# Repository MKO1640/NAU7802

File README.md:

# NAU7802

first try to make a PCB Breakout for NAU7802 

BOM:
1 x NAU7802SGI SOIC-16_3.9x9.9mm_P1.27mm
1 x PinHeader_1x06_P2.54mm_Vertical
1 x PinHeader_1x04_P2.54mm_Vertical
2 x PinHeader_1x01_P2.54mm_Vertical
4 x R_0805_2012Metric 47 Ohm 
4 x C_0805_2012Metric 0,1uF
2 x C_0805_2012Metric   1uF
1 x Wago_734-135_1x05_P3.50mm_Vertical
1 x C_0805_2012Metric 330pF

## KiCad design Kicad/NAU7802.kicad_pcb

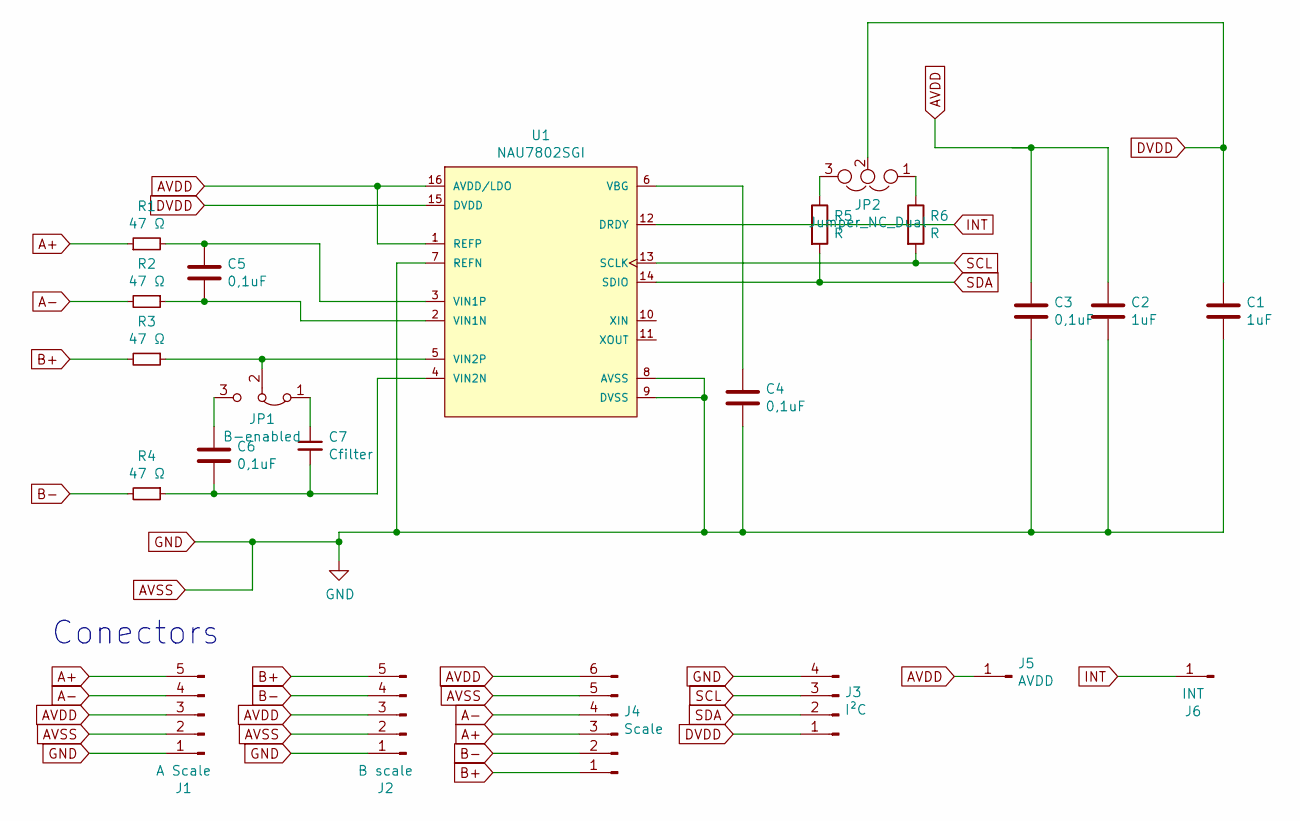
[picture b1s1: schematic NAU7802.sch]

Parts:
C1, C2: 1uF; C_0805_2012Metric
C3, C4, C5, C6: 0,1uF; C_0805_2012Metric
C7: Cfilter; C_0805_2012Metric
J1: A Scale; PinHeader_1x05_P2.54mm_Vertical
J2: B scale; Wago_734-135_1x05_P3.50mm_Vertical
J3: I²C; PinHeader_1x04_P2.54mm_Vertical
J4: Scale; PinHeader_1x06_P2.54mm_Vertical
J5: AVDD; PinHeader_1x01_P2.54mm_Vertical
J6: INT; PinHeader_1x01_P2.54mm_Vertical
JP1: B-enabled; SolderJumper-3_P1.3mm_Open_RoundedPad1.0x1.5mm
JP2: Jumper_NC_Dual; SolderJumper-3_P1.3mm_Open_RoundedPad1.0x1.5mm
R1, R2, R3, R4: 47 Ω; R_0805_2012Metric
R5, R6: R; R_0805_2012Metric
U1: NAU7802SGI; SOIC-16_3.9x9.9mm_P1.27mm; digikey description IC ADC 24BIT I2C/SRL 16-SOP

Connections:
A+: J1.5, J4.3, R1.1
A-: J1.4, J4.4, R2.2
AVDD: C2.1, C3.1, J1.3, J2.3, J4.6, J5.1, U1.1 (REFP), U1.16 (AVDD/LDO)
AVSS: C1.2, C2.2, C3.2, C4.2, J1.1, J1.2, J2.1, J2.2, J3.4, J4.5, U1.7 (REFN), U1.8 (AVSS), U1.9 (DVSS)
B+: J2.5, J4.1, R3.2
B-: J2.4, J4.2, R4.2
DVDD: C1.1, J3.1, JP2.2, U1.15 (DVDD); also elsewhere on the board
INT: J6.1, U1.12 (DRDY)
unnamed: C4.1, U1.6 (VBG)
unnamed: C5.1, R1.2, U1.3 (VIN1P)
unnamed: C5.2, R2.1, U1.2 (VIN1N)
unnamed: C6.1, JP1.3 (B)
unnamed: C6.2, C7.2, R4.1, U1.4 (VIN2N)
unnamed: C7.1, JP1.1 (A)
unnamed: JP1.2 (C), R3.1, U1.5 (VIN2P)
unnamed 15: JP2.1, R6.1; also elsewhere on the board
unnamed 16: JP2.3, R5.1; also elsewhere on the board
SCL: J3.3, R6.2, U1.13 (SCLK)
SDA: J3.2, R5.2, U1.14 (SDIO)

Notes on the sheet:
Conectors

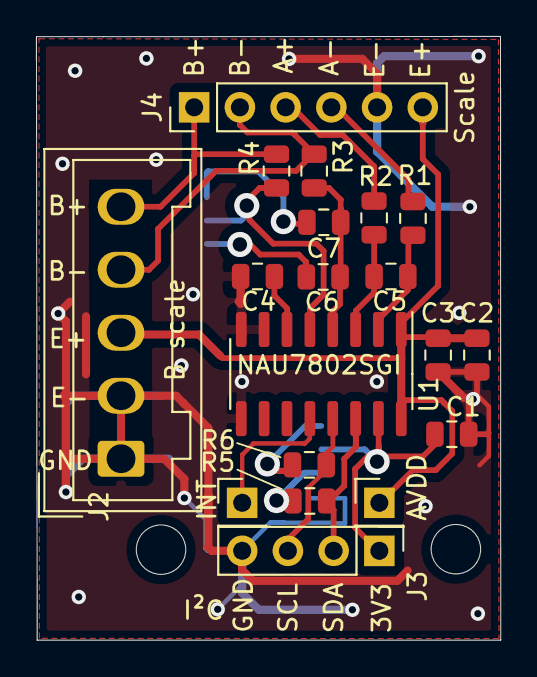
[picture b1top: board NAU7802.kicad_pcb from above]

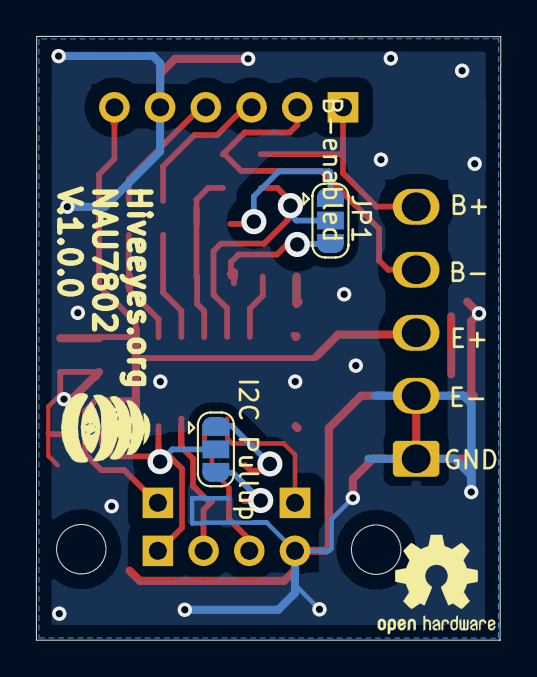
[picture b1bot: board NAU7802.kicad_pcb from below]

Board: 2 copper layers, 25.8 x 33.5 mm, 21 parts (2 on the bottom side), 19 nets.

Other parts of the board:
I2C Pullup: Jumper_NC_Dual; SolderJumper-3_P1.3mm_Open_RoundedPad1.0x1.5mm

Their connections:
DVDD: I2C Pullup.2; also elsewhere on the board
unnamed 15: I2C Pullup.1; also elsewhere on the board
unnamed 16: I2C Pullup.3; also elsewhere on the board

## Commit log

2020-07-05 Move to Path
2020-07-06 Update README.md
    Ad BOM
2020-07-07 ADD I²C Pullup + Jumper
2020-07-16 add v1.4
